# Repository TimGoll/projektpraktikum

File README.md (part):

# Dokumentation des Projektpraktikums
Projektpraktikum (Mikrocontrollerpraktikum + Messtechnikpraktikum) Winter- + Sommersemester 2016/17 am LMT

_Tim Goll, Matthias Baltes, Matthias Jost, Markus Herrmann-Wicklmayr_

## Aktuelle Demonstrationsvideos:
[Demovideo 1 (03.12.2016)](https://www.youtube.com/watch?v=2sz4_vMzZEc) <br>
[Demovideo 2 (04.06.2017)](https://www.youtube.com/watch?v=daKc67VaTdY)

## Verwendete Bibliotheken:
1. [**mThread**](http://www.kwartzlab.ca/2010/09/arduino-multi-threading-librar/): <br>
 Erstellt Pseudothreads auf dem Board, die nacheinander ausgeführt werden. Jeder Thread hat seine eigene ```loop()```. <br>
 Threads werden hinzugefügt mittels ```main_thread_list -> add_thread(CLASSNAME)```, anschließend laufen sie unbegrenzt weiter. **Hinweis:** Es sind anscheinend maximal 10 Threads möglich.

2. [**newdel**](https://github.com/jlamothe/newdel): <br>
 Fügt die Keywörter ```new``` und ```delete``` hinzu. Wird für mThread benötigt und musste leicht angepasst werden, damit sie auf neueren Arduino-Boards funktioniert.

3. [**QueueList**](http://playground.arduino.cc/Code/QueueList): <br>
 Fügt verkettete Listen hinzu, welche beliebige Datentypen speichern können. **Hinweis:** Es ist nicht möglich Pointer in ihnen zu speichern.

4. [**Adafruit BME280**](https://github.com/adafruit/Adafruit_BME280_Library) und [**Adafruit Sensor**](https://github.com/adafruit/Adafruit_Sensor): <br>
  Ansteuerung des Boschsensors (Die Version im Repo ist leicht verändert).

## Programmablauf:
1. Programm startet automatisch nach Herstellung der Stromversorgung.
2. Es kann ein Programm per USB von LabView übertragen werden, oder - falls eine SD-Karte eingesteckt ist - ein Programm von der SD-Karte aus gestartet werden.
3. Programm liest Daten (werden überprüft) und startet nach einem Tasterdruck/"Start"-Befehl.
4. Arbeitet Eventlisten ab, gibt Debug-Informationen aus, sofern über Schalter aktiviert, während der Laufzeit einstellbar.
5. Im Idle-Modus nach vollständiger Abarbeitung aller Events; nach Abschluss des Programms leuchtet eine LED und das Display leuchtet grün.
6. Zum Starten eines weiteren Programms muss das Board zurückgesetzt werden.
7. Es sind maximal 14.000 Events auf dem Board möglich. Dann ist der Speicher voll.
8. Für eine korrekte Steuerung muss **mindestens ein Ventil und ein MFC** existieren, sonst kommt es zu Fehlern. Falls in der Steuerung kein MFC/Ventil gebraucht wird, kann man auch einen leeres pseudo MFC/Ventil hinzufügen, das keine Events hat. Dafür muss nicht einmal Hardware angeschlossen sein.

## Übertragungsprotokoll (LabView -> Mikrocontroller):
Die Übertragung erfolgt zeilenweise in einem möglichst übertragungssicheren Format. Als Anfangs- und Endzeichen dienen zur Überprüfung der Vollständigkeit jeweils eine öffnende und eine schließende spitze Klammer. Alle Zeitangaben sind in Millisekunden. Es gibt nur ganzzahlige Integerwerte.

Die IDs der MFCs und Ventile ergeben sich jeweils aus der gegebenen Reihenfolge startend bei null.

**Zeilenweise Betrachtung der Übertragung**:

1. ```<Anzahl MFC, Anzahl Ventile>```
2. ```<Adresse MFC 0, Adresse MFC 1, ...>```
3. ```<Typ MFC 0, Typ MFC 1, ...>```
4. ```<Ventilplatinenadresse1, ...>``` Hexadezimale Ventilplatinenadressen
5. ```<Platinen-ID Ventil-Pin-ID, Platinen-ID Ventil-Pin-ID, ...>```
6. ```<Messintervall>``` Mess- und Speicherintervall in Millisekunden
7. ```<Datum + Zeit>``` Aktuelles Datum & Uhrzeit. Wird im Header der Messung gespeichert, relativ dazu wird gemessen
8. ```<begin>``` Ende des Headers, Beginn mit der Eventübertragung
9. ```<MFC oder Ventil, ID, Wert, Zeit>``` Setze Events. Hierbei müssen die Events je MFC/Ventil zeitlich sortiert sein, um eine einfachere Verarbeitung zu gewährleisten. Untereinander dürfen die Events jedoch vertauscht sein. (Zeit von MFC2 darf vor MFC1 sein, auch bei späterer Übertragung. Jedoch darf Zeit von MFC1 nicht vor der Zeit von MFC1 sein)
10. ```<end>``` Ende der Eventübertragung, warte auf Start der Messung
11. ```<start>``` Nicht zwingend notwendig, kann auch manuell per Taster gestartet werden

**Beispiel**:

```
<6,9>
<adresse0,adress1,adresse2,adresse3,adresse4,adresse5>
<typ0,typ1,typ2,typ3,typ4,typ5>
<0x20>
<0 0, 0 1, 0 2, 0 3, 0 4, 0 6, 0 9, 0 12, 0 15>
<10>
<08.02.2017-13:03:29>
<begin>
<M,0,120,1000>
<M,0,240,1500>
<M,1,170,800>
<M,0,150,1700>
...
<V,0,1,1200>
...
<end>
<start>
```

**Softwarereset**: Es ist auch möglich, das Board per Software neu zu starten. Dafür muss ein ```reset``` Befehl übertragen werden, woraufhin das Board neu startet und anschließend wieder ein ```ready``` ausgibt. (Hardwareimplementierung noch ausstehend). Weiteres siehe Ausblick.

## Serielle Kommunikation:
Vier Ports des Boards werden verwendet. Port 0 dient zur Kommunikation mit LabView (IN/OUT), Port 1 gibt Debug-Nachrichten aus, sofern der Debug-Schalter am Board aktiviert ist. Zur Kommunikation mit den MFCs dient Port 2.

Es gibt eine extra Klasse namens ```serialCommunication```, welche die Kommunikation über die vier Ports verwaltet. Zu Beginn muss in der ```setup()```-Funktion der Hauptino das Objekt initialisiert werden:
```cpp
srl->setSerial(&Serial1, &Serial3, &Serial2, &Serial4); //labview / debug / mks / buerkert
```
Anschließend kann man an beliebiger Stelle im Programm diese Klasse einfach nutzen:
```cpp
srl->print('D', "Hallo Welt!"); //(Typ: L, D, M, B / Ausgabetext)
srl->println('D', "Hallo Welt mit Zeilenende!"); //Natuerlich gibt es das ganze auch mit Linebreak
```
Der Typ der Ausgabe entscheidet, welcher Port genutzt wird. Hierbei gibt es drei Typen: L, D und M, B für LabView, Debug, MKS und Bürkert. Die Parameter, wie die Baudrate, werden in der **config.h** eingestellt.

Über den LabView-Port wird nach erfolgreicher Initialisierung des Boards ein _"ready"_ gesendet. Wurde ein Befehl korrekt erkannt und erfolgreich verarbeitet, wird ein _"ok"_ gesendet, andernfalls kommt ein Errorcode. Nach Abschluss einer Messung wird eine _"finished"_ Zeile übertragen.

## Serielle Hardware
Die Verbindung zwischen dem Teensy und dem PC über eine serielle Verbindung wird mit dem IC **CH340G** realisiert. Dieser funktioniert Plug and Play unter Windows (Windows 10 getestet) und lässt sich auch [mit einfachen Treibern](https://github.com/adrianmihalko/ch340g-ch34g-ch34x-mac-os-x-driver) unter MacOS zum Laufen bringen.

## SD Karte
Das SD-System des Teensy basiert auf FAT, daher sind Dateinamen maximal acht Zeichen lang (Großbuchstaben). Dateinamen, die länger als diese acht Zeichen sind, werden automatisch gekürzt (8.3 Format). Beim Speichern in eine Datei ist es jedoch wichtig, dass der Dateiname maximal 8 Zeichen hat, ansonsten tritt ein Fehler auf.

Die SD-Karte wird nur einmal beim Programmstart initialisiert. Es ist also nicht möglich, sie während der Laufzeit einzustecken oder zu entfernen. Ersteres wird nicht erkannt, letzteres führt zu Datenverlust. Wenn eine SD-Karte beim Programmstart erkannt wird, so wird dies durch ein Zeichen in der linken oberen Ecke gezeigt.

Eine neue SD-Karte kann einfach in den Leseslot gesteckt werden, alle nötigen Verzeichnisse werden automatisch erstellt. (Board muss resettet werden!)

### Messergebnisse
**Namensschema:** ```YYMMDDXX```<br>
Datum in Zweierschreibweise, zwei X für eine fortlaufende Nummerierung. Es sind maximal 100 (0..99) Messungen an einem Tag möglich. Falls der Zähler die 100 Überschreitet, werden kontinuierlich Messungen unter der Nummer _"xx"_ abgespeichert und überschrieben.

Beim Speichern auf der SD-Karte wird eine Datei mit einem Dateinamen, der das Datum und die Messungsnummer (falls mehrere Messungen pro Tag) enthält, erzeugt. Im gleichen Zuge wird in der txt-Datei ein Header in Klartext erstellt. Dieser enthält wesentliche Informationen wie die Startuhrzeit (diese stammt aus dem Header des Programms) der Messungen, die Anzahl der MFC's und Ventile, sowie die Typen der MFC's.

#### Beispielmessung
```
Messung am:     17.03.2017-22:12:46
Messintervall:  100
Anzahl Ventile: 6
Anzahl MFCs:    4
Typen der MFCs: MKS MKS MKS MKS

Wertsortierung: Laufzeit (ms), MFC Soll, MFC Ist, Ventil Soll, Bosch (Temp /C, Druck /Pa, Feucht /%)

0   0 0 0 0 0 0 0 0 0 0 0 0 0 0 22.520000 99050.312500 53.992188
100 0 0 0 0 0 0 0 0 0 0 0 0 0 0 22.520000 99050.312500 53.992188
200 0 0 0 0 0 0 0 0 0 0 0 0 0 0 22.520000 99048.062500 54.057617
300 0 0 0 0 0 0 0 0 0 0 0 0 0 0 22.520000 99042.750000 54.057617
.........
```

### Programme
1. Einzelne Befehlzeilen werden mit einem ```\n``` (Zeilenumbruch) voneinander getrennt.
2. Die Befehlszeilen werden bei Dateien **nicht** mit ```<``` und ```>``` umschlossen.
3. Leerzeilen und Leerzeichen werden ignoriert
4. Ebenso wird alles in einer Zeile nach einem ```#``` ignoriert, somit sind Kommentare möglich.
5. Dateinamen sind im FAT 8.3 Format und dürfen nicht mit ```.``` oder ```_``` beginnen.
6. Programme müssen sich im Ordner ```programs``` auf der SD Karte befinden.

#### Beispielprogramm
Nach dem Einstecken einer neuen SD Karte und dem Neustart des Boards wird eine Beispielprogrammdatei auf der SD Karte erstellt, die wie folgt aussieht:

```
# DIES IST EINE BEISPIELDATEI.
# Dateinmane duerfen nicht mit '.' oder '_' beginnen, sonst werden sie ignoriert.
# Im Gegensatz zu einer LabView Uebertragung sind hier Kommentare moeglich.
# leere Zeilen und Leerzeichen werden ignoriert.

4,16 #(MFCs, Ventile) in Dateien werden keine Tags benutzt
01,21,07,14 #(MFC Adressen)
Buerkert,Buerkert,MKS,MKS #(MFC Typen)
0x20 #(Ventilplatinen Adressen)
0 0, 0 1, 0 2, 0 3, 0 4, 0 5, 0 6, 0 7, 0 8, 0 9, 0 10, 0 11, 0 12, 0 13, 0 14, 0 15 #(Ventil Pins)
250 #(Messintervall)
08.02.2017-13:03:29 #(Datumstring)

begin #Ende Header, uebertrage Eventliste

M,0,120,1000
V,0,1,1000
V,1,1,750

end #Uebertragung abgeschlossen
start #Optionaler automatischer Programmstart
```

## I2C
I2C wird als Hauptkommunikationsbus verwendet. Folgende Adressen sind belegt (In der Klammer stehen die alternativen Adressen):
- Display: 0x38 (--)
- BME280: 0x76 (0x77)
- IO Expander (Ventilplatine, PCA9555): 0x20 (0x21 .. 0x27)

## BME280
Der Boschsensor wird innerhalb der Klasse ```main_boschCom``` verwaltet. Dort wird ein bme-Objekt erstellt. Dieses Objekt wird geliefert von einer leicht angepassten Adafruit-Bibliothek. (Diese könnte man noch weiter reduzieren, da der ganze SPI Bereich eigentlich nicht gebraucht wird)

**Anschluss des Sensors:**<br>
Folgende Pinbelegung ergab sich nach einigem Durchmessen mit einem Multimeter. Bisher erwies sich dieses Layout als korrekt.
```
        +----\_/----+
    VDD |o         o|                     VDD und VDDIO   : 3V3
  VDDIO |o         o|                     GND             : 0V
    GND |o         o|                     SDO (Adresspin) : 0V (0x76), 3V3 (0x77)
    SDO |o         o|                     CSB             : 3V3
    SDA |o         o|                     SDA / SCL       : I2C Bus (3V3 level)
    SCL |o         o|
    CSB |o   |_|   o|
        |o         o|
        |o         o|
        |o         o|
        |o         o| (SCL)
        |o         o| (SDA)
        |o         o|
        |o         o|
        |           |
        +-----------+
```
Den Sensor auslesen kann man in der besagten ```main_boschCom``` mit folgenden Befehlen:
```cpp
this->bme280->readTemperature();
this->bme280->readPressure();
this->bme280->readHumidity();
```

## Ventile
Die Ventilsteuerung befindet sich auf einer eigenen Platine. Das hat die beiden Vorteile, dass zum einen Kurzschlüsse auf der Ventilplatine keinen Schaden an der Hauptsteuerung verursachen können und es zum anderen möglich ist, "beliebig" viele Ventile mit einem Mikrocontroller zu steuern.

Theoretisch sind bis zu 8 Ventilplatinen mit je 16 Ventilen möglich, also insgesamt 128 Ventile. Auf der Platine befindet sich ein dreipoliger DIP-Switch zum Einstellen der Adresse (Adressraum: 0x20..0x27). Die Adressen sind bei Programmstart per LabView an den Controller zu übertragen. Jede der acht Platinen hat 16 Pins (0 bis 15), die auch bei der Initialisierung so angegeben werden müssen (```<Platinen-ID Pin-ID, ...>```). Intern haben die Ventile jedoch eine andere, fortlaufende, Nummerierung (siehe Übertragungsprotokoll).

Die softwareseitige Ansteuerung wird mittels einer kleinen von uns geschriebenen Bibliothek namens ```pca9555``` (Name des I2C ICs) realisiert. Angelehnt an die Syntax der Arduino-Umgebung gibt es auch hier eine ```digitalWrite(pinNumber)```-Funktion, der Einfachheit halber haben wir jedoch auf weitere Funktionen verzichtet und bei Porgammstart werden automatisch alle Pins als Ausgang definiert.

## Display:
Das Display ist via I2C mit dem Board verbunden, die Hintergrundbeleuchtung funktioniert mittels drei PWM Anschlüssen, einer für jede Grundfarbe. Daraus können beliebige Hintergrundfarben erzeugt werden. <br>
Je nach Meldungstyp ist die Hintergrundfarbe unterschiedlich. Folgende Typen gibt es:

- **Unkritische Fehler**: Error Code Level 1000; Dies sind Fehler, die beispielsweise bei der Kommunikation auftreten, aber keinen Programmabbruch benötigen. Sie werden auf dem Display für 2 Sekunden angezeigt. Farbe: _orange_
- **Kritische Fehler**: Error Code Level 5000; Diese Fehler führen zu einem Abbruch des Programms und werden auf dem Display angezeigt bis der Fehler behoben wurde. Farbe: _rot_

Standardmäßig werden auf dem Display aktuelle Daten zum Programmstatus angezeigt.

**Beispielanzeige**:
```
STANDARD:                      ERRORBEISPIEL:                 ENDANZEIGE:
+----------------------+       +----------------------+       +----------------------+
|          #M:04 #V:07 |       |      ERROR 1001      |       |          #M:04 #V:07 |
|                      |       |                      |       |                      |
| LAUFZEIT:00:01:34:17 |       |       Falscher       |       |    ABGESCHLOSSEN     |
| V03-0001-00:01:16:22 |       |     Zeilenbeginn     |       |     02:05:24:34      |
+----------------------+       +----------------------+       +----------------------+
Hintergrund: weiß              Hintergrund: organge/rot       Hintergrund: grün
```

- **Standardanzeige:** <br>
 Zeile 1: Anzahl MFCs und Anzahl Ventile <br>
 Zeile 2: xxx <br>
 Zeile 3: Laufzeit der Software, relativ zum Messstart <br>
 Zeile 4: Letztes Event, Typ-ID-Wert-Zeit
- **Erroranzeige:** <br>
 Zeile 1: Error ID <br>
 Zeile 2: xxx <br>
 Zeile 3+4: Kurzbeschreibung des aufgetretenen Fehlers
- **Endanzeige:** <br>
 Zeigt durchgängig diesen Text an, lässt sich nur zurücksetzen durch Reset des Boards

## Errormeldungen:
Bei allen Fehlermeldungen im 1000er Bereich wird das Programm weiterhin ausgeführt, es wird jedoch eine Wiederholung der entsprechenden Zeile erwartet, daher sind diese Codes LabView-seitig abzufangen.

### 1000:
**Maximale Input-String Länge überschritten.** In der _config.h_ wird eine Zeichenanzahl definiert, die pro Zeile gesendet werden darf. Diese Länge darf nicht überschritten werden.

### 1001:
**Falscher Zeilenbeginn.** Die Zeile muss mit einer öffnenden spitzen Klammer ```<``` begonnen werden, damit sie als gültig akzeptiert wird. Dies dient der Vollständigkeitsüberprüfung.

### 1002:
**Falsches Zeilenende.** Die Zeile muss mit einer schließenden spitzen Klammer ```>``` beendet werden, damit sie als gültig akzeptiert wird. Dabei darf man jedoch nicht vergessen, dass die Stringeingabe mit einem Zeilenumbruch ```\n``` als vollständig markiert wird. Dies dient der Vollständigkeitsüberprüfung.

### 1003:
**Lese-Timeout überschritten.** In der _config.h_ wird eine maximale Lesezeit pro String definiert. Wird diese Zeit überschritten, wird das Lesen des Strings an dieser Stelle abgebrochen.

### 1004:
**Falsche Anzahl an Argumenten.** Bei der Übertragung von LabView an den Controller wird immer überprüft, ob die Anzahl an eingetroffenen Elementen der Anzahl an erwarteten Elementen entspricht.

### 5000:
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
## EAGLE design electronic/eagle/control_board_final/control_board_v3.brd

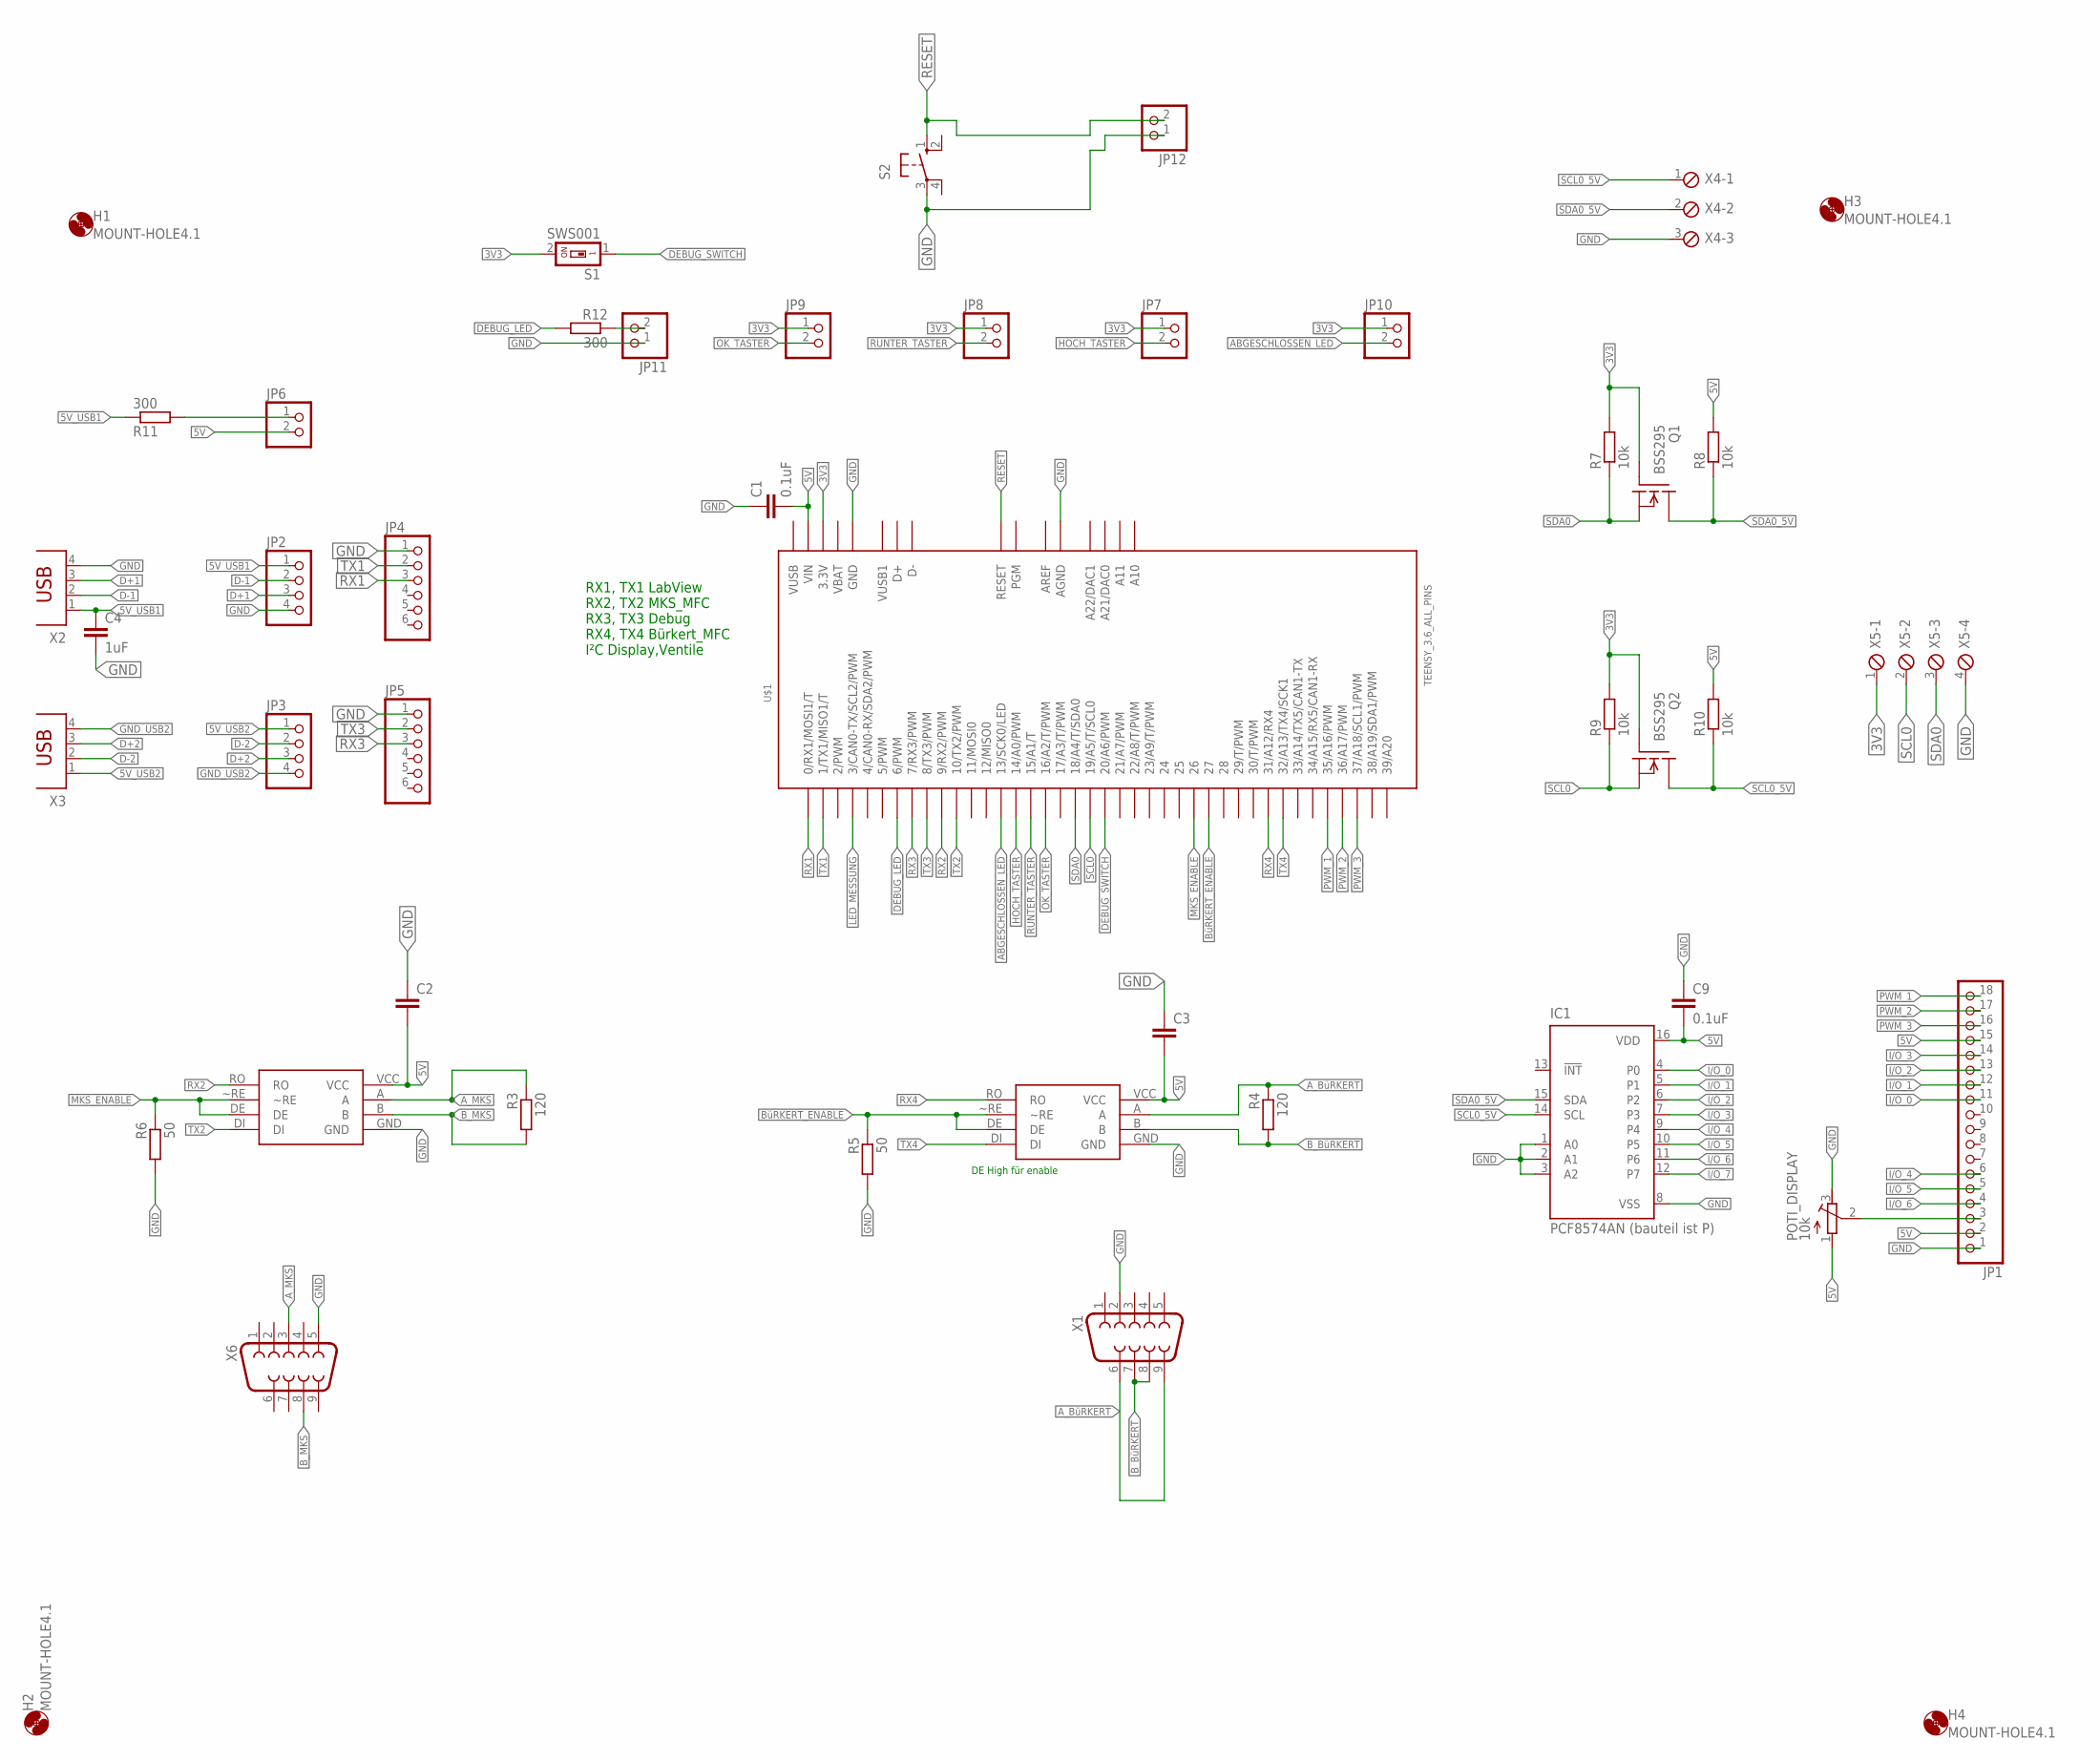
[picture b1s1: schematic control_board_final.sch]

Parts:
C1, C9: 0.1uF; C0805
C2, C3: C-EUC0805; C0805
C4: 1uF; C0805
H1, H2, H3, H4: MOUNT-HOLE4.1; 4,1
IC1: PCF8574AN (bauteil ist P); DIL16
JP1: PINHD-1X18; 1X18
JP2, JP3: PINHD-1X4; 1X04
JP4, JP5: PINHD-1X6; 1X06
JP6, JP7, JP8, JP9, JP10, JP11, JP12: PINHD-1X2; 1X02
POTI_DISPLAY: 10k; RTRIM3374
Q1, Q2: BSS295; TO92
R3, R4: 120; R0805
R5, R6: 50; R0805
R7, R8, R9, R10: 10k; VMTA55
R11, R12: 300; R0805
S1: SWS001; SMS-001
S2: 10-XX; B3F-10XX
U$1: TEENSY_3.6_ALL_PINS
U$5, U$6: MAX14775EASA+; SO08
X1, X6: F09HP
X2, X3: PN61729
X4: MPT3; 3POL254
X5: MPT4; 4POL254

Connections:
3V3: JP7.1, JP8.1, JP9.1, JP10.1, Q1.1 (G), Q2.1 (G), R7.2, R9.2, S1.2, U$1.3.3V, U$1.3.3V3 (3.3V), U$1.3.3V4 (3.3V), X5.1
5V: C1.2, C2.2, C3.2, C9.2, IC1.16 (VDD), JP1.2, JP1.15, JP6.2, POTI_DISPLAY.1 (A), R8.2, R10.2, U$1.VIN, U$5.VCC, U$6.VCC
5V_USB1: C4.1, JP2.1, R11.1, X2.1
5V_USB2: JP3.1, X3.1
ABGESCHLOSSEN_LED: JP10.2, U$1.13 (13/SCK0/LED)
AREF: U$1.AREF
A_BüRKERT: R4.1, U$5.A, X1.6, X1.9
A_MKS: R3.1, U$6.A, X6.3
B_BüRKERT: R4.2, U$5.B, X1.7, X1.8
B_MKS: R3.2, U$6.B, X6.8
BüRKERT_ENABLE: R5.1, U$1.27, U$5.DE, U$5.~RE
D+1: JP2.3, X2.3
D+2: JP3.3, X3.3
D-1: JP2.2, X2.2
D-2: JP3.2, X3.2
DEBUG_LED: R12.2, U$1.6 (6/PWM)
DEBUG_SWITCH: S1.1, U$1.20/A6 (20/A6/PWM)
GND: C1.1, C2.1, C3.1, C4.2, C9.1, IC1.1 (A0), IC1.2 (A1), IC1.3 (A2), IC1.8 (VSS), JP1.1, JP2.4, JP4.1, JP5.1, JP11.1, JP12.1, POTI_DISPLAY.3 (E), R5.2, R6.2, S2.3, U$1.AGND, U$1.GND, U$1.GND1 (GND), U$1.GND3 (GND), U$1.GND4 (GND), U$1.GND6 (GND), U$5.GND, U$6.GND, X1.2, X2.4, X4.3, X5.4, X6.5
GND_USB2: JP3.4, X3.4
HOCH_TASTER: JP7.2, U$1.14/A0 (14/A0/PWM)
I/O_0: IC1.4 (P0), JP1.11
I/O_1: IC1.5 (P1), JP1.12
I/O_2: IC1.6 (P2), JP1.13
I/O_3: IC1.7 (P3), JP1.14
I/O_4: IC1.9 (P4), JP1.6
I/O_5: IC1.10 (P5), JP1.5
I/O_6: IC1.11 (P6), JP1.4
I/O_7: IC1.12 (P7)
LED_MESSUNG: U$1.3 (3/CAN0-TX/SCL2/PWM)
MKS_ENABLE: R6.1, U$1.26, U$6.DE, U$6.~RE
unnamed: JP6.1, R11.2
unnamed: JP11.2, R12.1
OK_TASTER: JP9.2, U$1.16/A2 (16/A2/T/PWM)
POTI: JP1.3, POTI_DISPLAY.2 (S)
PWM_1: JP1.18, U$1.35/A16 (35/A16/PWM)
PWM_2: JP1.17, U$1.36/A17 (36/A17/PWM)
PWM_3: JP1.16, U$1.37/A18 (37/A18/SCL1/PWM)
RESET: JP12.2, S2.1 (S), U$1.RESET
RUNTER_TASTER: JP8.2, U$1.15/A1 (15/A1/T)
RX1: JP4.3, U$1.0 (0/RX1/MOSI1/T)
RX2: U$1.9 (9/RX2/PWM), U$6.RO
RX3: JP5.3, U$1.7 (7/RX3/PWM)
RX4: U$1.31/A12 (31/A12/RX4), U$5.RO
SCL0: Q2.3 (S), R9.1, U$1.19/A5 (19/A5/T/SCL0), X5.2
SCL0_5V: IC1.14 (SCL), Q2.2 (D), R10.1, X4.1
SDA0: Q1.3 (S), R7.1, U$1.18/A4 (18/A4/T/SDA0), X5.3
SDA0_5V: IC1.15 (SDA), Q1.2 (D), R8.1, X4.2
TX1: JP4.2, U$1.1 (1/TX1/MISO1/T)
TX2: U$1.10 (10/TX2/PWM), U$6.DI
TX3: JP5.2, U$1.8 (8/TX3/PWM)
TX4: U$1.32/A13 (32/A13/TX4/SCK1), U$5.DI
VBAT: U$1.VBAT
VUSB: U$1.VUSB
VUSB1: U$1.VUSB1

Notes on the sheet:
RX1, TX1 LabView RX2, TX2 MKS_MFC RX3, TX3 Debug RX4, TX4 Bürkert_MFC I²C Display,Ventile
DE High für enable

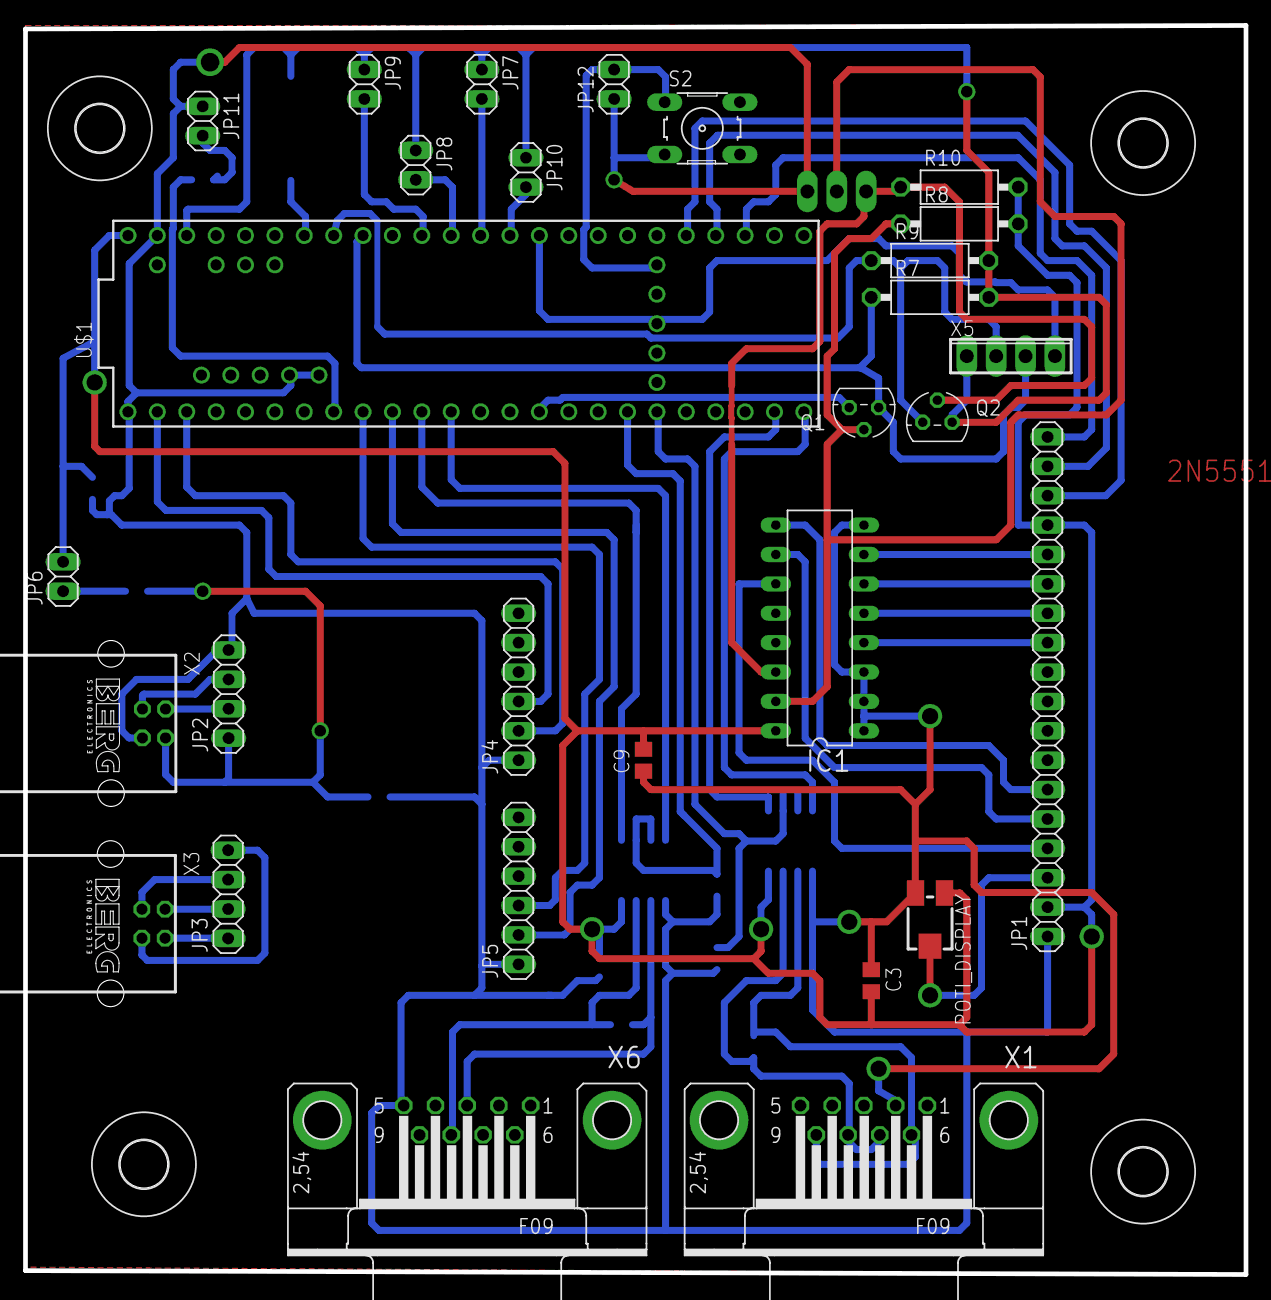
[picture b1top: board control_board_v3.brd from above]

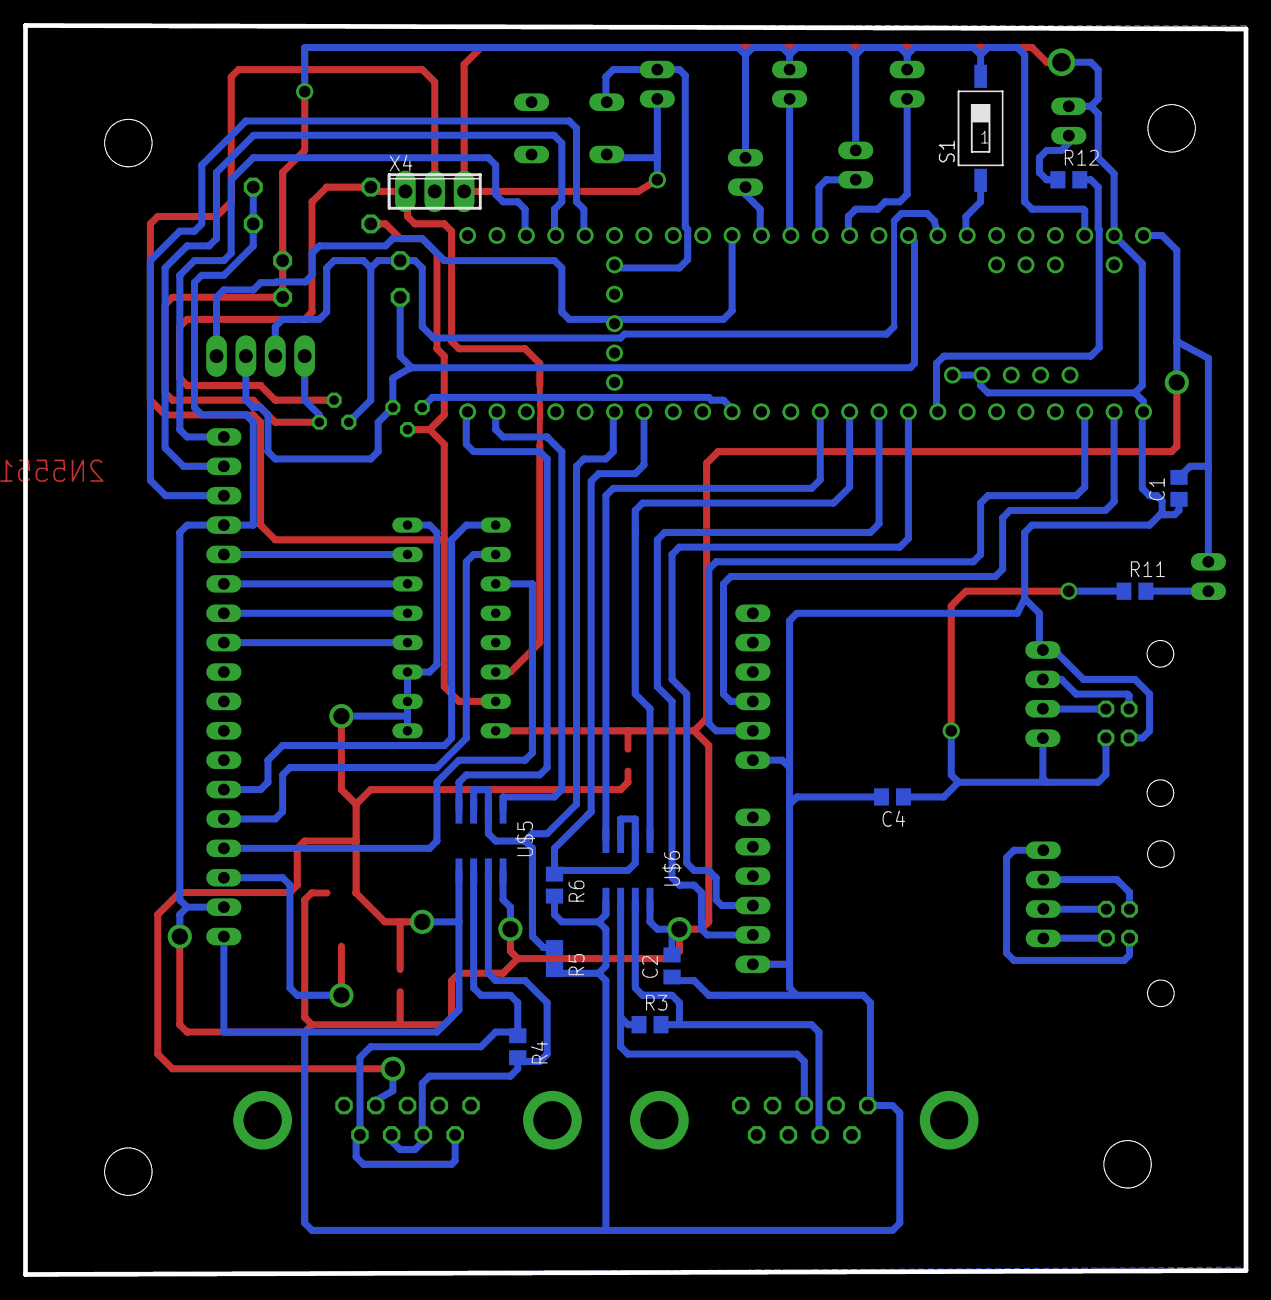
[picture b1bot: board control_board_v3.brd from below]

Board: 2 copper layers, 105.5 x 108.0 mm, 46 parts (13 on the bottom side), 48 nets.

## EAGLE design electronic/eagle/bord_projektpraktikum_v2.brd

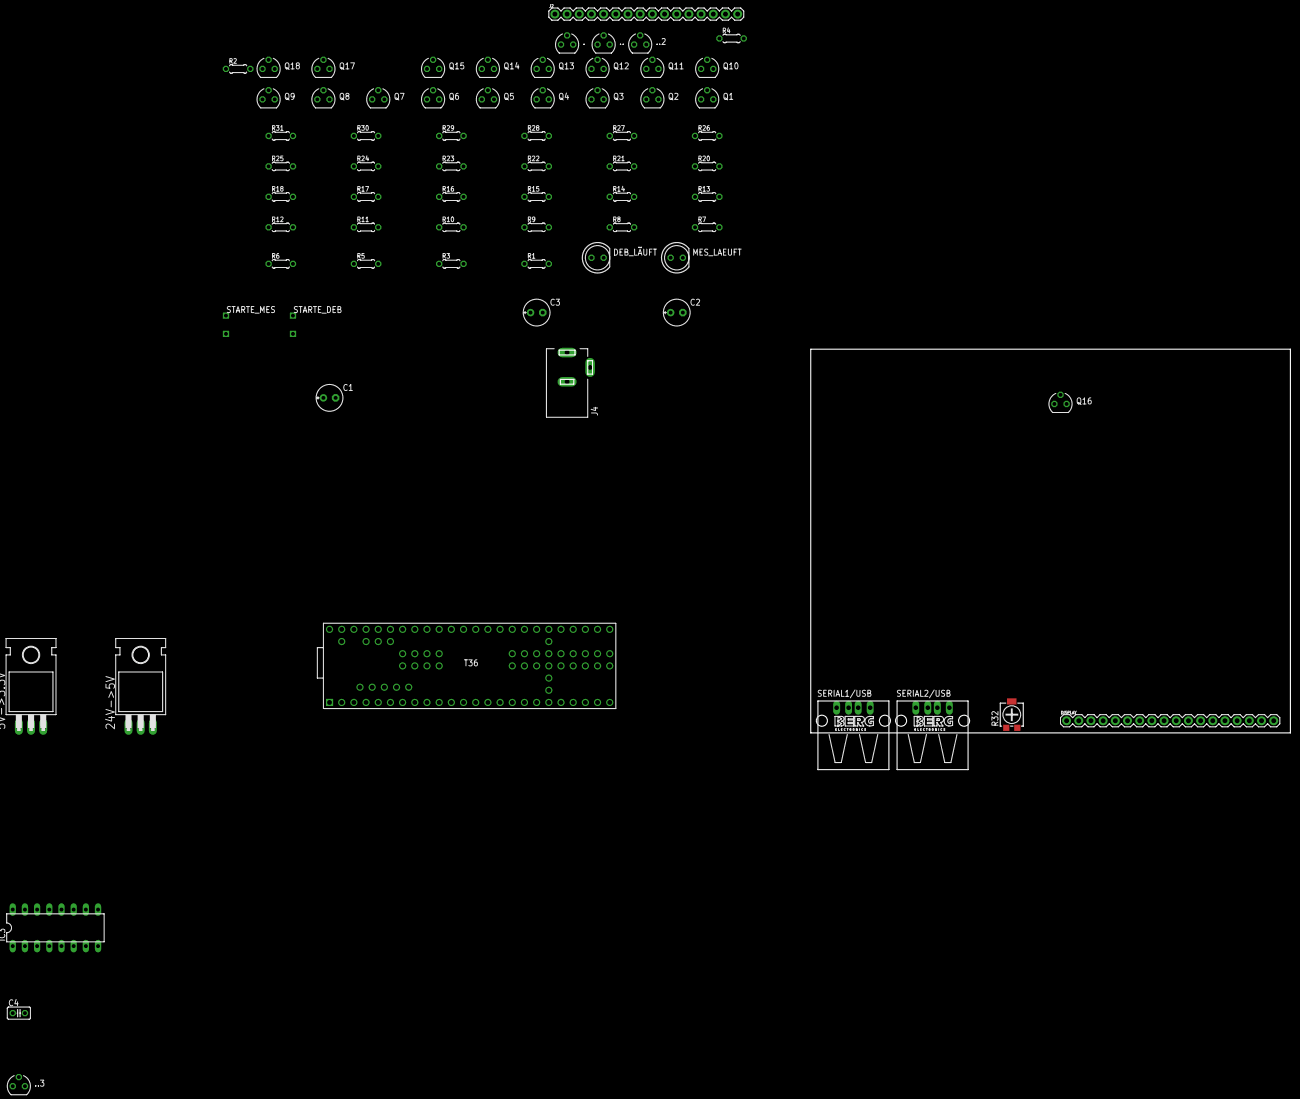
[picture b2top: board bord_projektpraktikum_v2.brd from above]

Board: 2 copper layers, 152.4 x 80.0 mm, 70 parts (0 on the bottom side), 65 nets, no tracks yet.

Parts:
5V->3.3V: TSR 1-2433; TO220H
24V->5V: TSR 1-2450; TO220H
., .., ..2, ..3: SOT54E
C1, C2, C3: E2,5-6E
C4: C025-025X050
DEB_LÄUFT: LED5MM
DISPLAY: 1X18
IC3: DIL16
J2: 1X16
J4: 24V; DCJ0303
MES_LAEUFT: LED5MM
Q1, Q2, Q3, Q4, Q5, Q6, Q7, Q8, Q9, Q10, Q11, Q12, Q13, Q14, Q15, Q16, Q17, Q18: BS170; SOT54E
R1, R3, R5, R6, R7, R8, R9, R10, R11, R12, R13, R14, R15, R16, R17, R18: 0204/5
R2, R4: 200; 0204/5
R20, R21, R22, R23, R24, R25, R26, R27, R28, R29, R30, R31: 10K; 0204/5
R32: RTRIM4G/J
SERIAL1/USB, SERIAL2/USB: PN87520
STARTE_DEB: EINTASTER
STARTE_MES: EINTASTER
U$1: TEENSY3_6--ALLPINS; T36

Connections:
.: ..D, R26.1, SERIAL1/USB.2
GND: 5V->3.3V.2, 24V->5V.2, C1.-, C2.-, C3.-, C4.1, DISPLAY.1, IC3.1, IC3.2, IC3.3, IC3.8, J4.3, R1.1, R2.2, R3.1, R4.2, R5.1, R6.1, R7.1, R8.1, R9.1, R10.1, R11.1, R12.1, R13.1, R14.1, R15.1, R16.1, R17.1, R18.1, R32.3, SERIAL1/USB.3, SERIAL2/USB.3, U$1.G0, U$1.G1, U$1.G2, U$1.G3, U$1.G4, U$1.G5, U$1.G6
unnamed: ...S, R25.1, U$1.1
unnamed: ..2.S, R28.1, U$1.8
unnamed: ..3.D, R30.1, SERIAL2/USB.2
unnamed: ..2.D, R31.1, SERIAL2/USB.1
unnamed: STARTE_MES.14, U$1.38
unnamed: J2.16, Q1.D, R1.2
unnamed: DISPLAY.14, IC3.4
unnamed: 24V->5V.1, J4.1, Q1.S, Q2.S, Q3.S, Q4.S, Q5.S, Q6.S, Q7.S, Q8.S, Q9.S, Q11.S, Q13.S, Q14.S, Q15.S, Q16.S, Q17.S, Q18.S
unnamed: Q1.G, U$1.21
unnamed: J2.14, Q3.D, R5.2
unnamed: MES_LAEUFT.A, R2.1
unnamed: MES_LAEUFT.K, U$1.40
unnamed: DEB_LÄUFT.A, R4.1
unnamed: DEB_LÄUFT.K, U$1.39
unnamed: STARTE_DEB.13, U$1.37
unnamed: Q2.G, U$1.22
unnamed: J2.13, Q4.D, R6.2
unnamed: J2.12, Q5.D, R3.2
unnamed: Q4.G, U$1.24
unnamed: Q5.G, U$1.25
unnamed: DISPLAY.3, R32.2
unnamed: J2.8, Q9.D, R11.2
unnamed: J2.9, Q8.D, R10.2
unnamed: J2.7, Q11.D, R12.2
unnamed: Q8.G, U$1.28
unnamed: Q9.G, U$1.29
unnamed: Q11.G, U$1.30
unnamed: J2.1, Q17.D, R18.2
unnamed: J2.6, Q13.D, R13.2
unnamed: DISPLAY.11, IC3.7
unnamed: Q3.G, U$1.23
unnamed: J2.15, Q2.D, R8.2
unnamed: J2.11, Q6.D, R7.2
unnamed: J2.10, Q7.D, R9.2
unnamed: Q6.G, U$1.26
unnamed: Q7.G, U$1.27
unnamed: J2.5, Q14.D, R14.2
unnamed: J2.4, Q15.D, R15.2
unnamed: J2.3, Q16.D, R16.2
unnamed: J2.2, Q18.D, R17.2
unnamed: Q13.G, U$1.31
unnamed: Q14.G, U$1.32
unnamed: Q15.G, U$1.33
unnamed: Q16.G, U$1.34
unnamed: Q18.G, U$1.35
unnamed: Q17.G, U$1.36
unnamed: 5V->3.3V.3, ..G, ...G, ..2.G, ..3.G, Q10.G, Q12.G, R20.2, R22.2, R24.2, R25.2, R28.2, R29.2
unnamed: DISPLAY.13, IC3.5
unnamed: IC3.14, Q10.D, R21.2
unnamed: IC3.15, Q12.D, R23.2
unnamed: Q12.S, R22.1, U$1.48
unnamed: DISPLAY.12, IC3.6
unnamed: DISPLAY.6, IC3.9
unnamed: DISPLAY.5, IC3.10
unnamed: DISPLAY.4, IC3.11
unnamed: ...D, R27.1, SERIAL1/USB.1
unnamed: ..3.S, R29.1, U$1.7
unnamed: Q10.S, R20.1, U$1.47
unnamed: 5V->3.3V.1, 24V->5V.3, C4.2, DISPLAY.15, IC3.16, R21.1, R23.1, R26.2, R27.2, R30.2, R31.2, R32.1, STARTE_DEB.14, STARTE_MES.13
unnamed: ..S, R24.1, U$1.0
unnamed: C3.+, DISPLAY.18, U$1.2
unnamed: C2.+, DISPLAY.17, U$1.3
unnamed: C1.+, DISPLAY.16, U$1.4

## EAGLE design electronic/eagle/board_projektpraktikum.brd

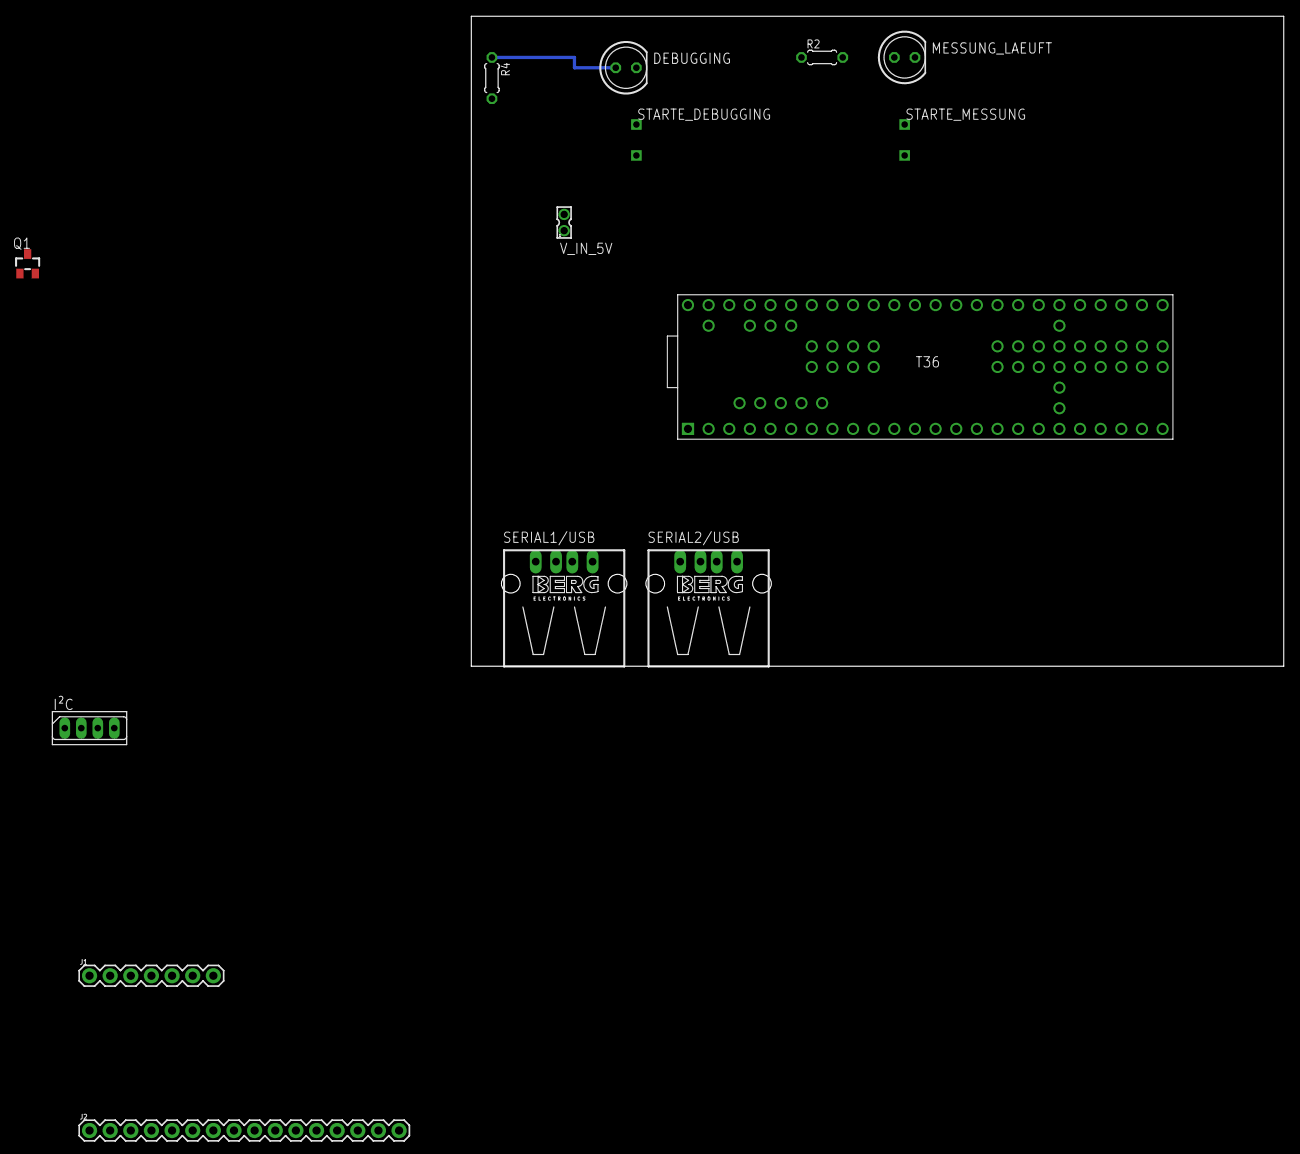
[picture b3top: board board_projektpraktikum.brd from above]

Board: 2 copper layers, 100.0 x 80.0 mm, 14 parts (0 on the bottom side), 9 nets.

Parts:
DEBUGGING: LED5MM
I²C: 01; SPB4
J1: 1X07
J2: 1X16
MESSUNG_LAEUFT: LED5MM
Q1: BSS138; SOT23
R2, R4: 200; 0204/5
SERIAL1/USB, SERIAL2/USB: PN87520
STARTE_DEBUGGING: EINTASTER
STARTE_MESSUNG: EINTASTER
U$1: TEENSY3_6--ALLPINS; T36
V_IN_5V: 87758-0216

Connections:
DISPLAY: J1.6, J1.7, SERIAL1/USB.4, SERIAL2/USB.4, STARTE_DEBUGGING.13, U$1.5V, U$1.10, V_IN_5V.1
GND: J1.1, R2.2, R4.2, SERIAL1/USB.3, SERIAL2/USB.3
unnamed: J1.5, U$1.14
unnamed: STARTE_MESSUNG.14, U$1.40
unnamed: MESSUNG_LAEUFT.A, R2.1
unnamed: MESSUNG_LAEUFT.K, U$1.41
unnamed: DEBUGGING.A, R4.1
unnamed: DEBUGGING.K, U$1.56
unnamed: STARTE_DEBUGGING.14, U$1.55

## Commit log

2016-11-18 Initialer Commit mit der Dateistruktur
2016-11-18 added Filestructure
2016-11-18 added filestructure 2
2016-11-21 New file structure, empty ino as arduino-main, node as program main
2016-11-22 1. Funktionierende Dateistruktur, die sich für das Arduino-Board kompilieren lässt
2016-11-23 Threads implementiert, funktionieren nun. Jede Klasse hat ihre eigene loop()-Funktion. Als Haupdatei dient nun wieder die *.ino-Datei
2016-11-26 mfcCtrl: erste in der Theorie funktionierende Steuerung fertiggestellt
2016-11-26 Fehlerverbesserungen + Übertragungsentwurf
2016-11-26 Erste Serielle Kommunikation in LabCom
2016-11-27 LabCom weiter geführt, Objekte und Threads für die MFCs werden nun in LabCom erstellt. Jedoch hängt sich das Board bei der Ausfuehrung noch immer auf...
2016-11-27 Bug gefixed, Scheint so, als seien maximal 10 Threads möglich
2016-11-28 MFC_MAIN Datei hinzugefügt
2016-11-29 Overflow-Bug gefixed (unsigned long gilt nun für 49,7 Tage) LabCom Code vereinfacht LabCom verarbeitet nun die komplette Eingabe: Header+EventList MFC-Event-Steuerung steht soweit
2016-11-29 Debugzeitausgabe beim MFC hinzugefügt
2016-11-30 Überarbeitete Dateistruktur, leichte Codeerweiterung Entwurf Schaltskizze
2016-11-30 Schaltskizze Ebenenfehler behoben
2016-11-30 labview ordner
2016-12-01 Überarbeitung Schaltplanskizze
2016-12-01 Dateikorrektur
2016-12-03 neue serialCommunication Klasse ValveCom "fertig" SwitchCase Struktur eingebaut Bugs fixed: Bug1 MFC-Spam/Abstürze / Bug2 0 und 1 Event pro Objekt führt nicht mehr zu Abstürzen
2016-12-03 Als Eingabenw werden nun Leerzeichen am Anfang+Ende entfernt
2016-12-12 displayklasse neu, leider noch buggy testskript (python)
2016-12-13 Display Bug gefixt, stürzt nicht mehr ab und zeigt richtige Daten an. Dokumentation aktualisiert
2016-12-13 Beschreibung aktualisiert
2016-12-16 DISPLAY UND KOMMUNIKATIONSUPDATE - RGB-LCD-Display wird unterstützt (Angepasste I2C_LCD Bibliothek wird hierfür verwendet) - Leere Eingabestrings (nur '\n') werden ignoriert - Fehlermeldungen werden 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
2016-12-17 WORKING DISPLAY UPDATE - neue LCD_I2C Bibliothek als Grundlage, funktioniert nun mit "PCF8574A"
2016-12-19 DISPLAY UPDATE - bessere Serielle Event-Ausgabe - deutlich schnellere Displayaktualisierung
2016-12-28 SDFat lib hinzugefügt, erste arbeite an StoreD
2016-12-28 examples in Sd lib gelöscht
2016-12-30 richtige SD lib benutzt, leichte Abänderung an StoreD
2017-01-05 Store_D abänderungen
2017-01-05 Teensyanpassung begonnen
2017-01-05 main_stringBuilder eingefügt (Pseudocode) main_StoreD--> StoreD (Klasse ist keine Mainklasse mit Loop mehr) StoreD Datei Beispiel Readme aktualisiert
2017-01-06 Platzhalter Klassen für StringBuilder und BoschCom eingegliedert, Austausch der Pointer, setzen der Initialisierungswerte Bug fixes Readme aktualisiert
2017-01-07 ZWISCHENUPDATE - main_labCom, main_valveCtrl, main_mfcCtrl enthalten nun die gebrauchten Funktionen für den String Builder - Threads von main_valveCtrl und main_mfcCtrl beenden sich nun automatisch n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
2017-01-12 Abänderung an StoreD
2017-01-12 Eagle ergänzt
2017-01-12 Readme geändert
2017-01-12 PNG von Schematic hinzugefügt
2017-01-13 Version 2 des Schaltplans
2017-01-13 Schematic aufgeräumt
2017-01-13 Größere Umstrukturierung bei StoreD; Arbeiten an Stringbuilder (Zeile zusammenbauen), in diesem Zusammenhang Hinzufügen von getValueXY-Funktionen
2017-01-15 Debugging von Main_StringBuilder, Hinzufügen des Kopfs einer Datei (Datum, Messintervall, Anzahl..) in StoreD
2017-01-15 jetzt völlig bugfrei
2017-01-19 Hinzufügen von Umwandlung einer MAX_ROW_BYTES Byte großen Zahl in Kette von pseudobinäre Zeichen (Funktion itpb(int value)) bisher noch char to const char errors
2017-01-19 errors durch itpb beseitigt
2017-02-02 Anpassungen von StringBuilder + Display leuchtet nun gruen nach Fertigstellung der Eventlisten
2017-02-07 Queue List fertig, wird nun auch an String Builder gesendet -> schliesst Datei / kleine Anpassungen / Datumsplatzhalter fuer Header /// noch nicht getestet
2017-02-07 rm .DS_Store
2017-02-09 Anpassungen für Datumsanzeige
2017-02-09 attachInterrupt() hinzugefügt
2017-02-09 updated Readme - Hardwareplaung
2017-02-28 Update Readme.md, neuer USB<->Uart IC
2017-03-01 Erstellen eines Header in der txt-Datei beim öffnen dieser. Abänderungen an integerToByte.
2017-03-01 alle nach der Änderung aufgetretenen Fehlermeldungen behoben
2017-03-02 kleine Änderung an integerToByte, StoreD und main_stringBuilder
2017-05-27 BME UPDATE - bme Bibliothek von Adafruit rausgesucht und etwas umgeschrieben, Sensor lässt sich nun ansprechen - srl Klasse um "read(constchar type)" und "available(const char type)" erweitert. Somit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
2017-05-28 PCA9555 Eigene Bibliothek zur Ansteuerung des PCA9555 via I2C geschrieben (Test mit Hardware steht noch aus)
2017-05-28 REFACTORING - int, long, ... durch uint8_t, uint16_t, uint32_t ersetzt (und ohne unsigned) - Ventilplatine nun auch in Steuerung komplett eingebunden - Bugs gefixt (und hoffentlich keine neuen eingeb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
2017-05-30 CRASH GEFIXT - zufällige Abstürze des Programmes sind nun behoben - LEDs + Taster implementiert, srl sendet nurnoch Debugnachrichten, wenn Pin 5 HIIGH ist - python script geupdated - kleinere Bugfixe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
2017-05-31 MFC RECHERCHE
2017-06-02 MFC Zwischenupdate
2017-06-03 SD-KARTEN-PROGRAMME UND DISPLAYMENÜ - alles etwas umstrukturiert - Menüführung auf dem Display zum Programmstart von der SD Karte - eigene "Interrupt"-Steuerung der Eingangspins (attachInterrupt() sc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
2017-06-04 TESTVERSION MIT VIDEO - vorerst fertige Version mit kleinen Details die noch ausstehen - scheint aktuell Bugfrei
2017-06-07 ungetestet: StoreD finalisiert, Tests müssen noch folgen
2017-06-07 push for pull
2017-06-07 mit debuggen begonnen
2017-06-09 Code mit StoreD und StringBuilder compiliert nun, ist aber noch zu testen. Programme können nun auch von der SD Karte gelesen werden
2017-06-13 SD UPDATE
    - Programme können nun problemlos von der SD Karte gelesen werden
    - beim Speichern gibt es noch Probleme mit den Strings
2017-06-14 SD UPDATE 2 - Dateien werden nun auch geschrieben: TODO Klartextspeichern, da Probleme mit ASCII - viele weitere Anpassungen
2017-06-18 KLEINIGEKEITEN - StoreD speichert nun in Klartext - StoreD speichert nun auch die MFC Typen - StoreD ignoriert nun leere Zeilen beim Lesen aus Textdatei - Boschsensor Werte werden nun (alle drei) auc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
2017-06-18 FILESYSTEM - Dateilisten beim Programmstart sind nun immer korrekt - Scrollen in der Liste ist nun auch bei weniger als drei Einträgen problemlos möglich - Systemdateien, die mit '_' oder '.' beginne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
2017-06-18 FILESYSTEM 2 - Dateinamen werden nun sortiert in Programmauswahl angezeigt - Die beiden Standardordner werden neu erzeugt, falls sie nicht vorhanden sind - es wird eine Beispieldatei im Programmordne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
2017-06-19 SD SYMBOL - kleines Symbol in der linken oberen Ecke zeigt, ob eine SD Karte gefunden wurde
2017-06-19 readme fix
2017-06-20 BUGFIXES - neuer Ladescreen, wodurch man erkennt, wann Steuerung bereit für Eingaben ist - Autostart in Programmdateien funktioniert nun - Keine "unendliche Messung" mehr, wenn es keine MFC oder Vent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
2017-06-23 FINALISIERUNGSUPDATE - I2C Clock läaft nun mit 200kHz, könnte nun bessere Displayperformance geben - Dateileseproblem behoben für Dateien, die mit normalen Char (nicht in Kommentar) enden - SD read T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
2017-06-24 BUGFIX - Tastereingaben während Messung werden nun wieder ignoriert - Ladestand in Prozent untersützt nun Dateien größer als 32768 Bytes (int Größe) - I2C Frequenz zurück auf 100kHz, da es sonst Prob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
2017-07-07 an neue Platine angepasst, Portänderungen + Configerweiterungen, neuer Serieller Port (MKS und Bürkert sind nun getrennt)
2017-07-11 MKS MFC TEST - Mks MFC Ansteuerung geht - Softwarereset - Display mit Ok/Start Knopf während Messung ausschaltbar - MFC Com Objekte funktionieren nun mit flush() und delayMicroseconds (nicht sehr sch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
2017-07-14 INTERRUPT - Interruptsteuerung für MFC Kommunikation um möglichst effizient zu kommunizieren
2017-08-16 MFC-UPDATE - kleinere Bugs gefixt, MKS MFCs bekommen nun korrekte Befehle gesendet, lesen Antwort per Interrupts aus - Antwort von MKS MFCs ist nicht lesbar. Hardwarefehler? - analog zu MKS MFCs habe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
2017-09-05 DOKU UND MFC - Doku aktualisiert - Labview hinzugefügt - MFCs (MKS) fertig und weitere kleine Änderungen
2017-09-06 Elektronik Teil der readme überarbeitet
2017-09-12 Neue Version des Control-Board
2017-09-12 Bild gewechselt
2017-09-16 README UPDATE - kleine Fehler behoben - Blockschaltbild hinzugefügt
2017-09-16 README UPDATE - kleiner Fix
2017-09-16 README UPDATE - kleiner Bildfix
2017-09-16 README UPDATE weiterer Bildfix
2017-09-16 README UPDATE weiterer kleiner Fix
2017-09-19 bürkert_pin_out
2017-11-11 changed main language, ignoring eagle files

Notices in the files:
parts and their libraries:
m-pad-2.1: License : GNU General Public License version 2 (see bottom)
SparkFun-Connectors: Licensing: Creative Commons ShareAlike 4.0 International - https://creativecommons.org/licenses/by-sa/4.0
